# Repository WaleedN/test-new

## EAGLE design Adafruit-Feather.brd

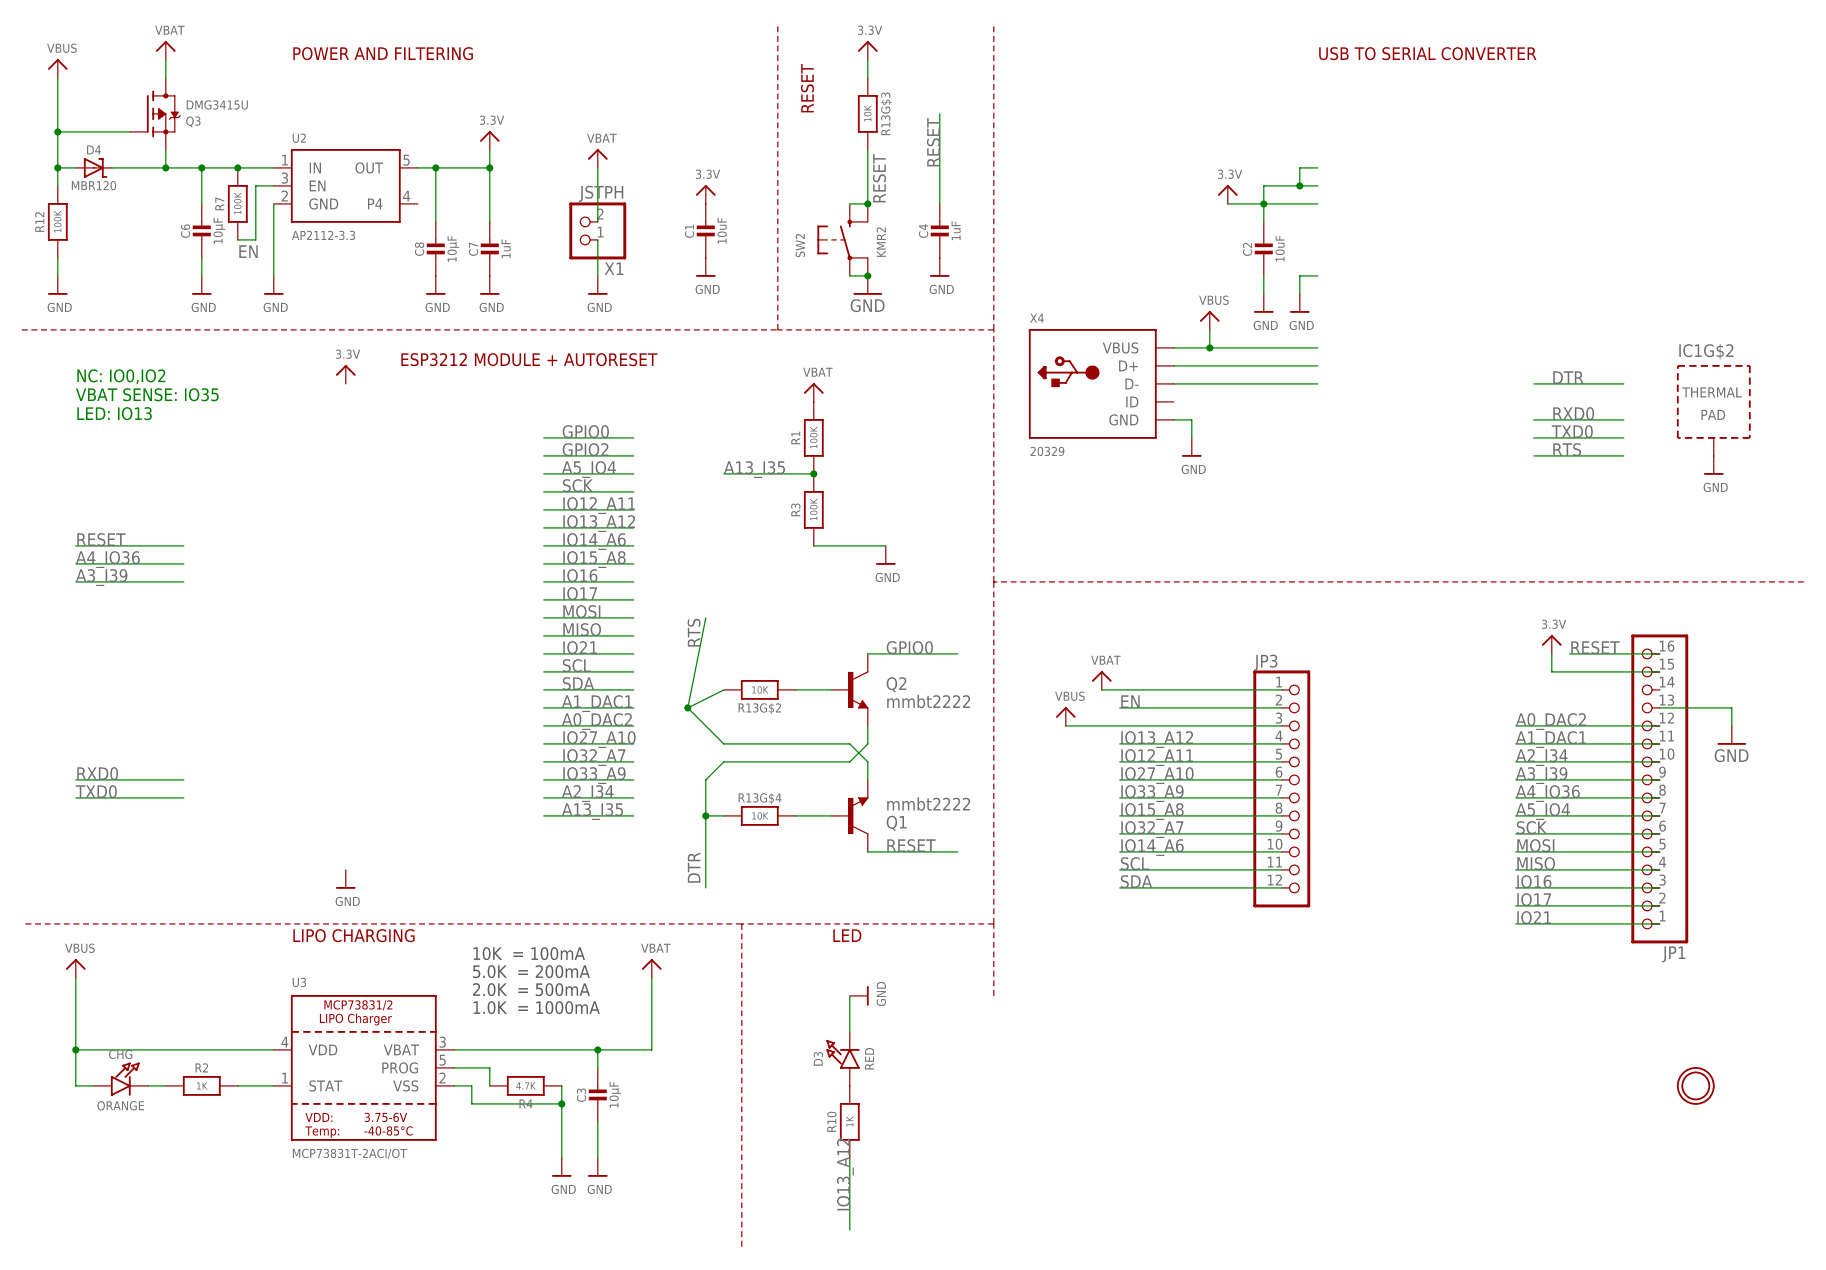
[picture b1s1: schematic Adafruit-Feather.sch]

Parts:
C1, C2: 10uF; 0805-NO
C3, C6, C8: 10µF; 0805-NO
C4, C7: 1uF; 0603-NO
CHG: ORANGE; CHIPLED_0805_NOOUTLINE
D3: RED; CHIPLED_0805_NOOUTLINE
D4: MBR120; SOD-123
IC1: CP2104; QFN24_4MM_SMSC
JP1: HEADER-1X16_MIN; 1X16_ROUND_MIN
JP3: HEADER-1X12_MIN; 1X12_ROUND_MIN
Q1, Q2: mmbt2222; SOT23-3
Q3: DMG3415U; SOT23-R
R1, R3, R7, R12: 100K; 0603-NO
R2, R10: 1K; 0603-NO
R4: 4.7K; 0603-NO
R13: 10K; RESPACK_4X0603
SW2: KMR2; BTN_KMR2_4.6X2.8
U2: AP2112-3.3; SOT23-5
U3: MCP73831T-2ACI/OT; SOT23-5
U$32: MOUNTINGHOLE2.5; MOUNTINGHOLE_2.5_PLATED
X1: JSTPH; JSTPH2
X4: 20329; 4UCONN_20329_V2

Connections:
3.3V: C1.1, C2.1, C7.1, C8.1, JP1.15, R13.3 (1), U2.5 (OUT)
A0_DAC2: JP1.12
A1_DAC1: JP1.11
A2_I34: JP1.10
A3_I39: JP1.9
A4_IO36: JP1.8
A5_IO4: JP1.7
A13_I35: R1.1, R3.2
DTR: Q2.2 (E), R13.4 (1)
EN: JP3.2, R7.1, U2.3 (EN)
GND: C1.2, C2.2, C3.2, C4.2, C6.2, C7.2, C8.2, D3.C, IC1.2 (GND), IC1.THERM (TP), JP1.13, R3.1, R4.1, R12.1, SW2.A, SW2.A' (P1), U2.2 (GND), U3.2 (VSS), X1.1, X4.BASE@1 (GND), X4.BASE@2 (GND), X4.GND, X4.SPRT@1 (GND), X4.SPRT@2 (GND), X4.SPRT@3 (GND), X4.SPRT@4 (GND)
GPIO0: Q2.3 (C)
IO12_A11: JP3.5
IO13_A12: JP3.4, R10.1
IO14_A6: JP3.10
IO15_A8: JP3.8
IO16: JP1.3
IO17: JP1.2
IO21: JP1.1
IO27_A10: JP3.6
IO32_A7: JP3.9
IO33_A9: JP3.7
MISO: JP1.4
MOSI: JP1.5
unnamed: CHG.C, R2.1
unnamed: R2.2, U3.1 (STAT)
unnamed: R4.2, U3.5 (PROG)
unnamed: D3.A, R10.2
unnamed: C6.1, D4.C, Q3.2 (S), R7.2, U2.1 (IN)
unnamed: Q1.1 (B), R13.5 (2)
unnamed: Q2.1 (B), R13.2 (1)
REGIN: IC1.7 (REGIN)
RESET: C4.1, JP1.16, Q1.3 (C), R13.6 (2), SW2.B (S), SW2.B' (S1)
RTS: Q1.2 (E), R13.7 (2)
SCK: JP1.6
SCL: JP3.11
SDA: JP3.12
VBAT: C3.1, JP3.1, Q3.3 (D), R1.2, U3.3 (VBAT), X1.2
VBUS: CHG.A, D4.A, IC1.8 (VBUS), JP3.3, Q3.1 (G), R12.2, U3.4 (VDD), X4.VBUS
VDD: IC1.6 (VDD)
VIO: IC1.5 (VIO)

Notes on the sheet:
POWER AND FILTERING
RESET
10K = 100mA
5.0K = 200mA
2.0K = 500mA
1.0K = 1000mA
USB TO SERIAL CONVERTER
LIPO CHARGING
LED
ESP3212 MODULE + AUTORESET
NC: IO0,IO2 VBAT SENSE: IO35 LED: IO13

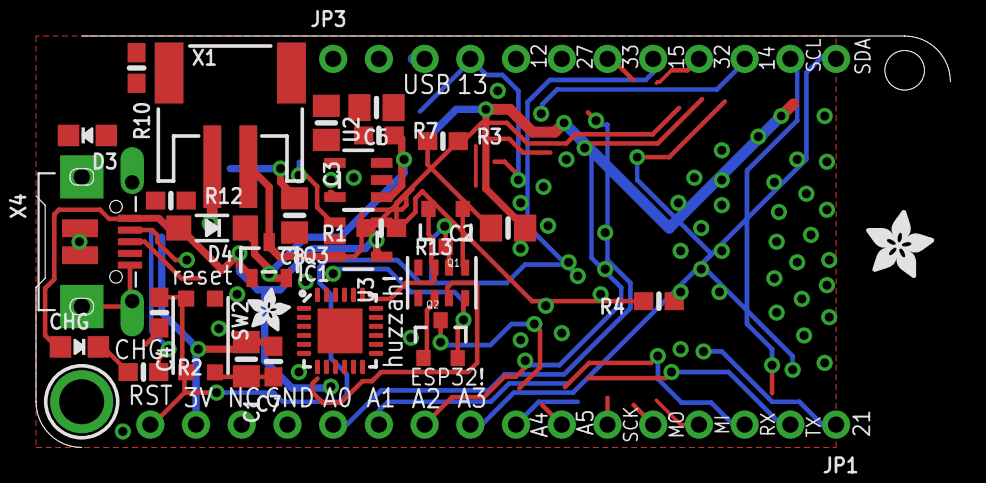
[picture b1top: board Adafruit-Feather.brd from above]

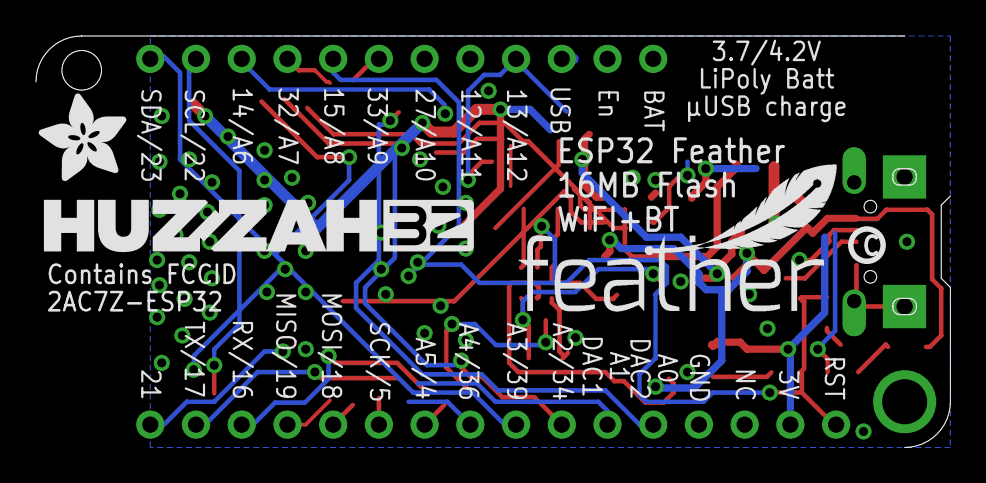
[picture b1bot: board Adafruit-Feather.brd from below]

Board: 2 copper layers, 50.8 x 22.9 mm, 36 parts (4 on the bottom side), 17 nets.

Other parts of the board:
U$7: ADAFRUIT_5MM
U$9: FEATHERLOGO_MED
U$13: PCBFEAT-REV-040
U$14: ADAFRUIT_2.5MM
U$15: ADAFRUIT_3.5MM
U$43: HUZZAH32

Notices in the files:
parts and their libraries:
microbuilder: This work is placed in the public domain, and may be freely used for commercial and non-commercial work with the following conditions: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
SparkFun: Licensing: CC v3.0 Share-Alike You are welcome to use this library for commercial purposes.
